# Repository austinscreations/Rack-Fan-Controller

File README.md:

# Rack-Fan-Controller
a controller that can monitor temperature in rack enclosures and control fans

2023-10-25 files have been updated and all JLCPCB PCBa files have now been included.

fan controller is a 4 layer PCB

breakout is 2 layers

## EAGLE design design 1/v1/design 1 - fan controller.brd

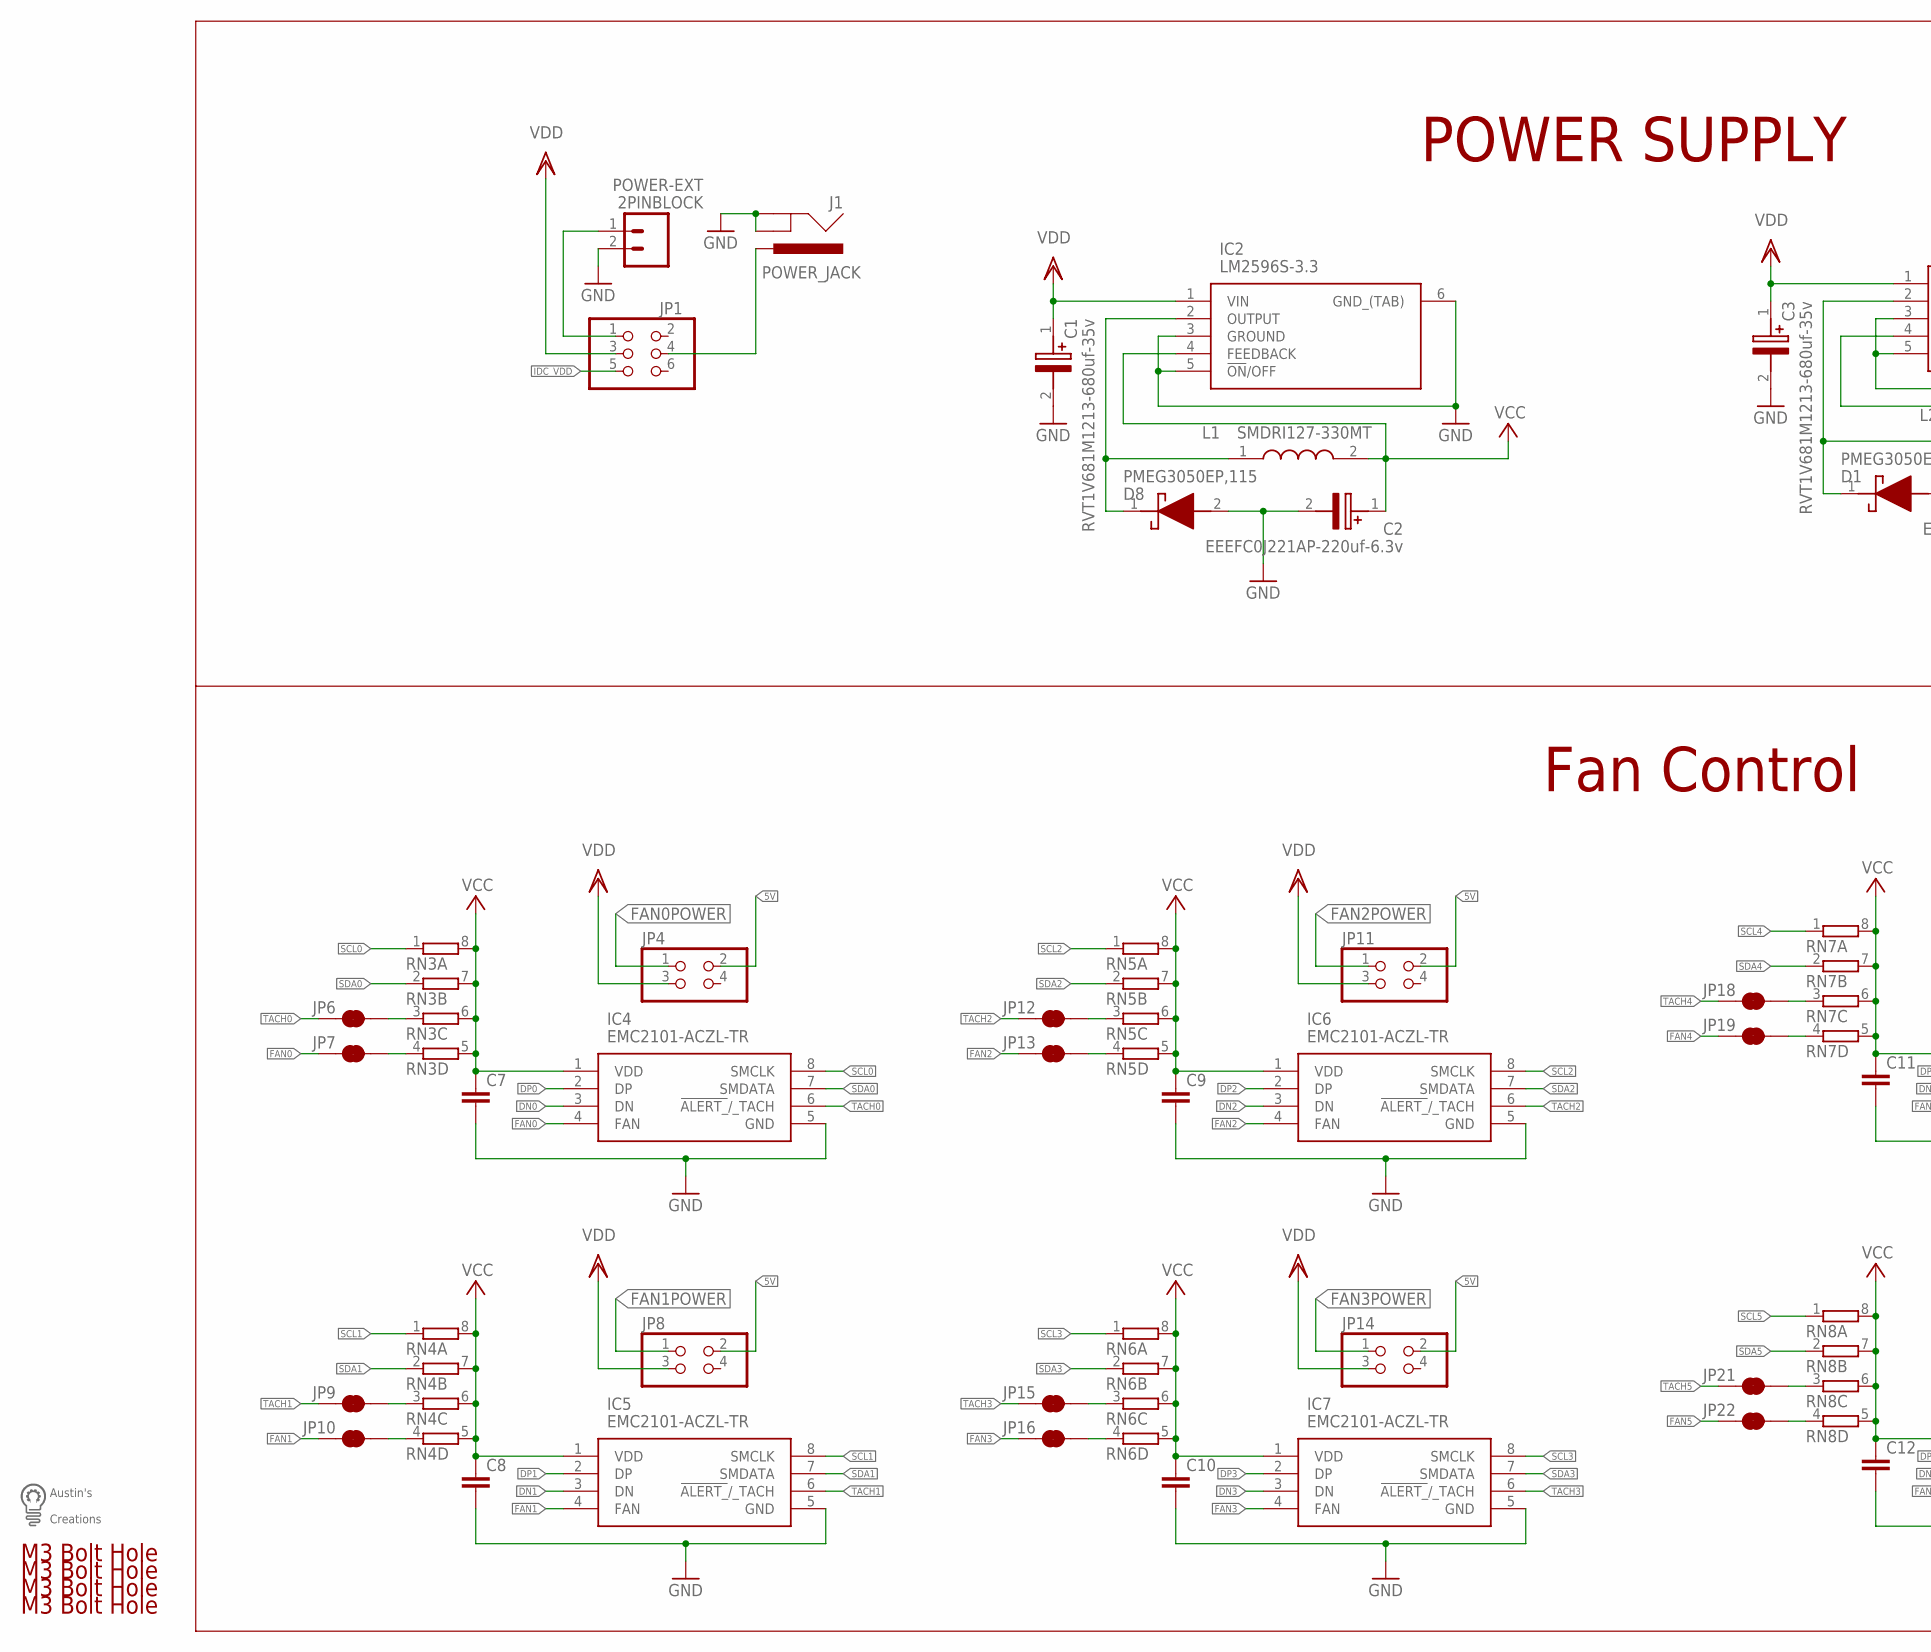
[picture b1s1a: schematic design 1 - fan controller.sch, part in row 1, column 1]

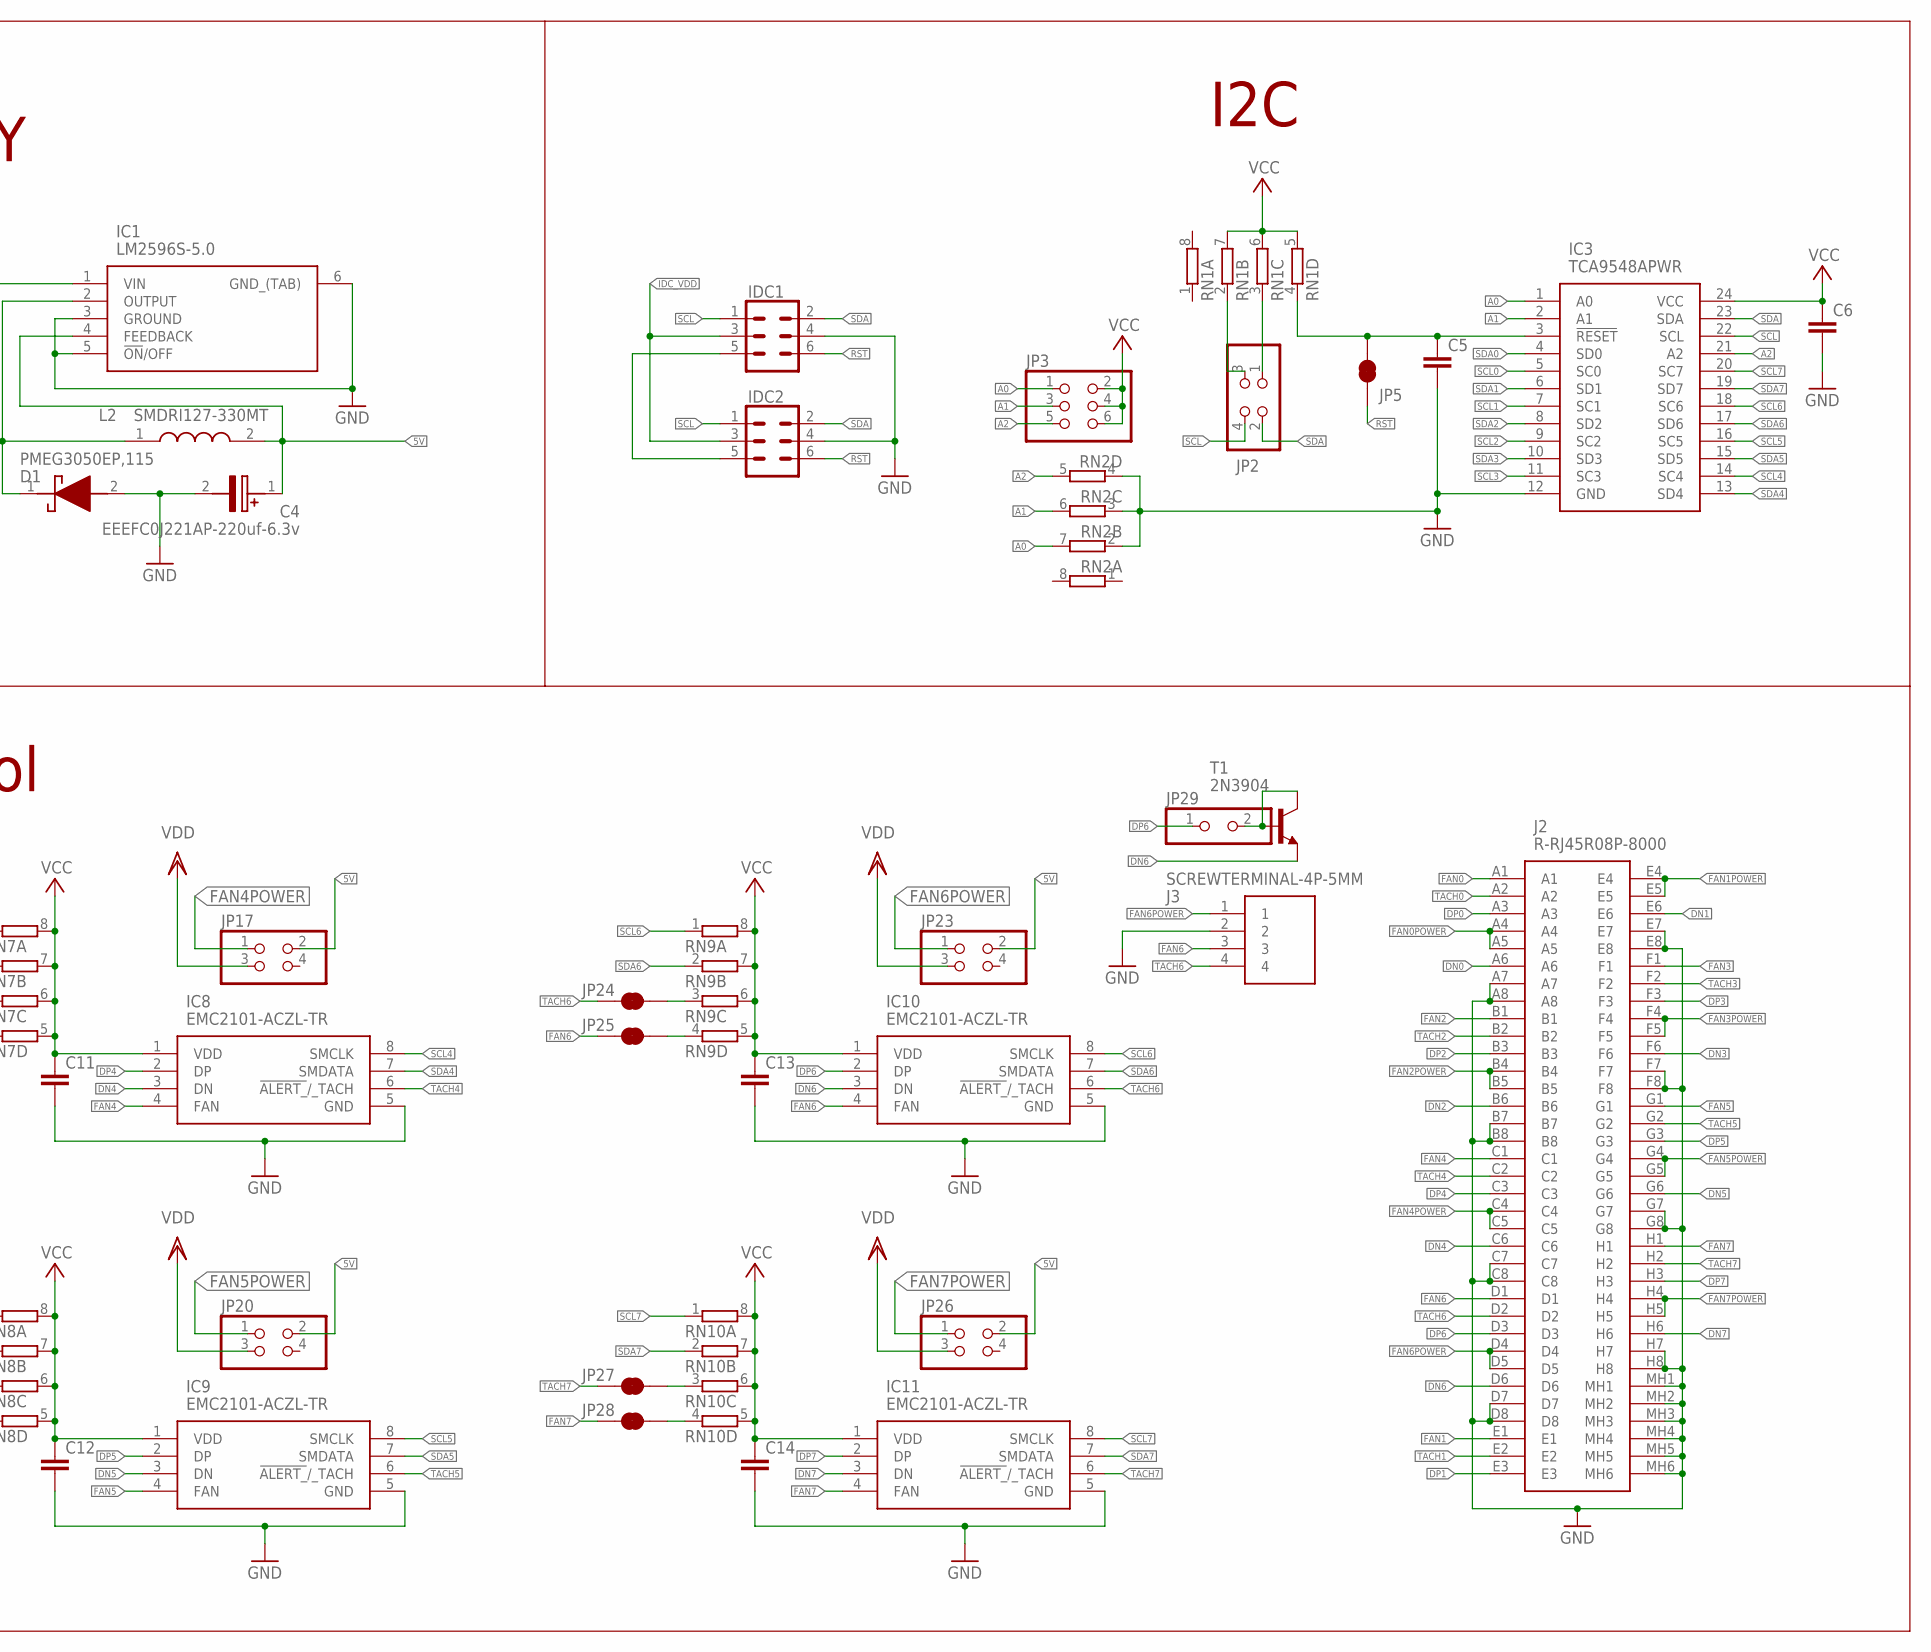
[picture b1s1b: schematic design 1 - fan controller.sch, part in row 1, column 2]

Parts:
C1, C3: RVT1V681M1213-680uf-35v; CAPAE1350X1400N
C2, C4: EEEFC0J221AP-220uf-6.3v; CAPAE830X650N
C5, C6, C7, C8, C9, C10, C11, C12, C13, C14: C-EUC0603; C0603
D1, D8: PMEG3050EP,115; PMEG3050EP115
IC1: LM2596S-5.0; TO170P1435X465-6N
IC2: LM2596S-3.3; TO170P1435X465-6N
IC3: TCA9548APWR; SOP65P640X120-24N
IC4, IC5, IC6, IC7, IC8, IC9, IC10, IC11: EMC2101-ACZL-TR; SOP65P490X110-8N
IDC1, IDC2: CONN_03X2SHROUD; 2X3-SHROUDED
J1: POWER_JACK; POWER_JACK_PTH
J2: R-RJ45R08P-8000; RRJ45R08P8000
J3: SCREWTERMINAL-4P-5MM
JP1, JP3: PINHD-2X3; 2X03
JP2, JP4, JP8, JP11, JP14, JP17, JP20, JP23, JP26: PINHD-2X2; 2X02
JP5, JP6, JP7, JP9, JP10, JP12, JP13, JP15, JP16, JP18, JP19, JP21, JP22, JP24, JP25, JP27, JP28: JUMPER-SMT_2_NC_TRACE_SILK; SMT-JUMPER_2_NC_TRACE_SILK
JP29: PINHD-1X2; 1X02
L1, L2: SMDRI127-330MT; INDPM120120X800N
POWER-EXT: 2PINBLOCK; SCREWTERMINAL-5MM-2
RN1, RN2, RN3, RN4, RN5, RN6, RN7, RN8, RN9, RN10: 4R-N0603-ARC; 0603-ARC
T1: 2N3904; TO92
U$1, U$2, U$3, U$4: M3BOLTHOLE
U$5: LOGOMED

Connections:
5V: C4.1 (+), IC1.4 (FEEDBACK), JP4.2, JP8.2, JP11.2, JP14.2, JP17.2, JP20.2, JP23.2, JP26.2, L2.2
$2: JP29.2, T1.1 (C), T1.2 (B)
A0: IC3.1 (A0), JP3.1, RN2.7 (2)
A1: IC3.2 (A1), JP3.3, RN2.6 (2)
A2: IC3.21 (A2), JP3.5, RN2.5 (2)
DN0: IC4.3 (DN), J2.A6
DN1: IC5.3 (DN), J2.E6
DN2: IC6.3 (DN), J2.B6
DN3: IC7.3 (DN), J2.F6
DN4: IC8.3 (DN), J2.C6
DN5: IC9.3 (DN), J2.G6
DN6: IC10.3 (DN), J2.D6, T1.3 (E)
DN7: IC11.3 (DN), J2.H6
DP0: IC4.2 (DP), J2.A3
DP1: IC5.2 (DP), J2.E3
DP2: IC6.2 (DP), J2.B3
DP3: IC7.2 (DP), J2.F3
DP4: IC8.2 (DP), J2.C3
DP5: IC9.2 (DP), J2.G3
DP6: IC10.2 (DP), J2.D3, JP29.1
DP7: IC11.2 (DP), J2.H3
FAN0: IC4.4 (FAN), J2.A1, JP7.1
FAN0POWER: J2.A4, J2.A5, JP4.1
FAN1: IC5.4 (FAN), J2.E1, JP10.1
FAN1POWER: J2.E4, J2.E5, JP8.1
FAN2: IC6.4 (FAN), J2.B1, JP13.1
FAN2POWER: J2.B4, J2.B5, JP11.1
FAN3: IC7.4 (FAN), J2.F1, JP16.1
FAN3POWER: J2.F4, J2.F5, JP14.1
FAN4: IC8.4 (FAN), J2.C1, JP19.1
FAN4POWER: J2.C4, J2.C5, JP17.1
FAN5: IC9.4 (FAN), J2.G1, JP22.1
FAN5POWER: J2.G4, J2.G5, JP20.1
FAN6: IC10.4 (FAN), J2.D1, J3.3, JP25.1
FAN6POWER: J2.D4, J2.D5, J3.1, JP23.1
FAN7: IC11.4 (FAN), J2.H1, JP28.1
FAN7POWER: J2.H4, J2.H5, JP26.1
GND: C1.2 (-), C2.2 (-), C3.2 (-), C4.2 (-), C5.2, C6.2, C7.2, C8.2, C9.2, C10.2, C11.2, C12.2, C13.2, C14.2, D1.2 (A), D8.2 (A), IC1.3 (GROUND), IC1.5 (!ON!/OFF), IC1.6 (GND_(TAB)), IC2.3 (GROUND), IC2.5 (!ON!/OFF), IC2.6 (GND_(TAB)), IC3.12 (GND), IC4.5 (GND), IC5.5 (GND), IC6.5 (GND), IC7.5 (GND), IC8.5 (GND), IC9.5 (GND), IC10.5 (GND), IC11.5 (GND), IDC1.4, IDC2.4, J1.GND, J1.GNDBREAK, J2.A7, J2.A8, J2.B7, J2.B8, J2.C7, J2.C8, J2.D7, J2.D8, J2.E7, J2.E8, J2.F7, J2.F8, J2.G7, J2.G8, J2.H7, J2.H8, J2.MH1, J2.MH2, J2.MH3, J2.MH4, J2.MH5, J2.MH6, J3.2, POWER-EXT.2, RN2.2 (1), RN2.3 (1), RN2.4 (1)
IDC_VDD: IDC1.3, IDC2.3, JP1.5
unnamed: D1.1 (K), IC1.2 (OUTPUT), L2.1
unnamed: C5.1, IC3.3 (!RESET), JP5.2, RN1.4 (1)
unnamed: JP6.2, RN3.3 (1)
unnamed: JP1.1, POWER-EXT.1
unnamed: JP7.2, RN3.4 (1)
unnamed: J1.PWR, JP1.4
unnamed: JP9.2, RN4.3 (1)
unnamed: JP10.2, RN4.4 (1)
unnamed: JP12.2, RN5.3 (1)
unnamed: JP13.2, RN5.4 (1)
unnamed: JP15.2, RN6.3 (1)
unnamed: IDC1.5, IDC2.5
unnamed: JP16.2, RN6.4 (1)
unnamed: JP18.2, RN7.3 (1)
unnamed: JP19.2, RN7.4 (1)
unnamed: JP21.2, RN8.3 (1)
unnamed: JP22.2, RN8.4 (1)
unnamed: JP24.2, RN9.3 (1)
unnamed: JP25.2, RN9.4 (1)
unnamed: D8.1 (K), IC2.2 (OUTPUT), L1.1
unnamed: JP27.2, RN10.3 (1)
unnamed: JP28.2, RN10.4 (1)
unnamed: JP2.3, RN1.2 (1)
unnamed: JP2.1, RN1.3 (1)
RST: IDC1.6, IDC2.6, JP5.1
SCL: IC3.22 (SCL), IDC1.1, IDC2.1, JP2.4
SCL0: IC3.5 (SC0), IC4.8 (SMCLK), RN3.1
SCL1: IC3.7 (SC1), IC5.8 (SMCLK), RN4.1
SCL2: IC3.9 (SC2), IC6.8 (SMCLK), RN5.1
SCL3: IC3.11 (SC3), IC7.8 (SMCLK), RN6.1
SCL4: IC3.14 (SC4), IC8.8 (SMCLK), RN7.1
SCL5: IC3.16 (SC5), IC9.8 (SMCLK), RN8.1
SCL6: IC3.18 (SC6), IC10.8 (SMCLK), RN9.1
SCL7: IC3.20 (SC7), IC11.8 (SMCLK), RN10.1
SDA: IC3.23 (SDA), IDC1.2, IDC2.2, JP2.2
SDA0: IC3.4 (SD0), IC4.7 (SMDATA), RN3.2 (1)
SDA1: IC3.6 (SD1), IC5.7 (SMDATA), RN4.2 (1)
SDA2: IC3.8 (SD2), IC6.7 (SMDATA), RN5.2 (1)
SDA3: IC3.10 (SD3), IC7.7 (SMDATA), RN6.2 (1)
SDA4: IC3.13 (SD4), IC8.7 (SMDATA), RN7.2 (1)
SDA5: IC3.15 (SD5), IC9.7 (SMDATA), RN8.2 (1)
SDA6: IC3.17 (SD6), IC10.7 (SMDATA), RN9.2 (1)
SDA7: IC3.19 (SD7), IC11.7 (SMDATA), RN10.2 (1)
TACH0: IC4.6 (!ALERT_!/_TACH), J2.A2, JP6.1
TACH1: IC5.6 (!ALERT_!/_TACH), J2.E2, JP9.1
TACH2: IC6.6 (!ALERT_!/_TACH), J2.B2, JP12.1
TACH3: IC7.6 (!ALERT_!/_TACH), J2.F2, JP15.1
TACH4: IC8.6 (!ALERT_!/_TACH), J2.C2, JP18.1
TACH5: IC9.6 (!ALERT_!/_TACH), J2.G2, JP21.1
TACH6: IC10.6 (!ALERT_!/_TACH), J2.D2, J3.4, JP24.1
TACH7: IC11.6 (!ALERT_!/_TACH), J2.H2, JP27.1
VCC: C2.1 (+), C6.1, C7.1, C8.1, C9.1, C10.1, C11.1, C12.1, C13.1, C14.1, IC2.4 (FEEDBACK), IC3.24 (VCC), IC4.1 (VDD), IC5.1 (VDD), IC6.1 (VDD), IC7.1 (VDD), IC8.1 (VDD), IC9.1 (VDD), IC10.1 (VDD), IC11.1 (VDD), JP3.2, JP3.4, JP3.6, L1.2, RN1.5 (2), RN1.6 (2), RN1.7 (2), RN3.5 (2), RN3.6 (2), RN3.7 (2), RN3.8 (2), RN4.5 (2), RN4.6 (2), RN4.7 (2), RN4.8 (2), RN5.5 (2), RN5.6 (2), RN5.7 (2), RN5.8 (2), RN6.5 (2), RN6.6 (2), RN6.7 (2), RN6.8 (2), RN7.5 (2), RN7.6 (2), RN7.7 (2), RN7.8 (2), RN8.5 (2), RN8.6 (2), RN8.7 (2), RN8.8 (2), RN9.5 (2), RN9.6 (2), RN9.7 (2), RN9.8 (2), RN10.5 (2), RN10.6 (2), RN10.7 (2), RN10.8 (2)
VDD: C1.1 (+), C3.1 (+), IC1.1 (VIN), IC2.1 (VIN), JP1.3, JP4.3, JP8.3, JP11.3, JP14.3, JP17.3, JP20.3, JP23.3, JP26.3

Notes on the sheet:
I2C
POWER SUPPLY
Fan Control

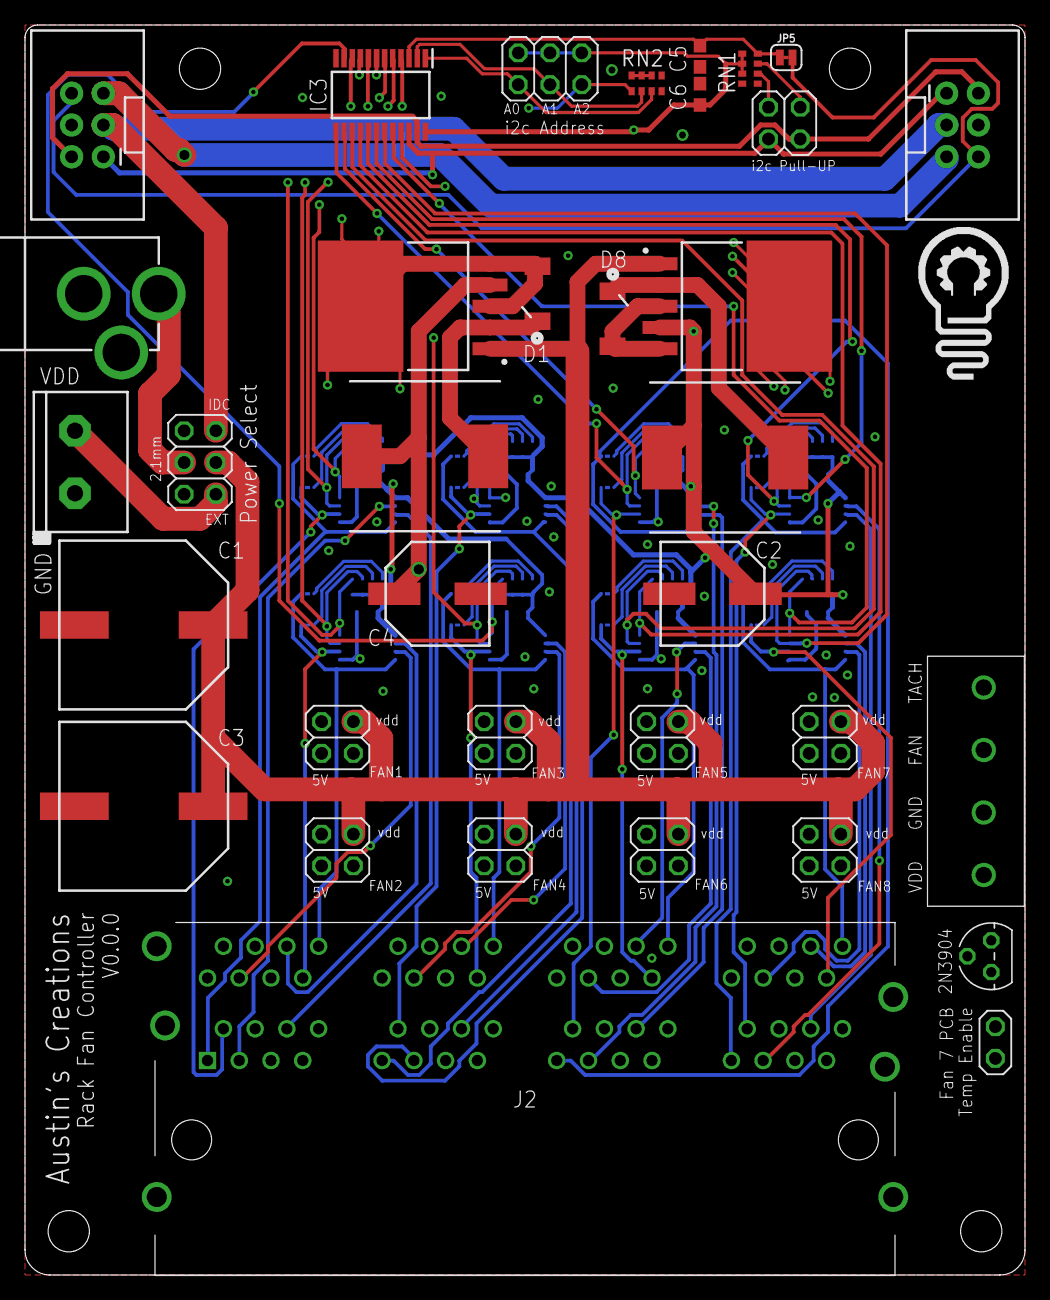
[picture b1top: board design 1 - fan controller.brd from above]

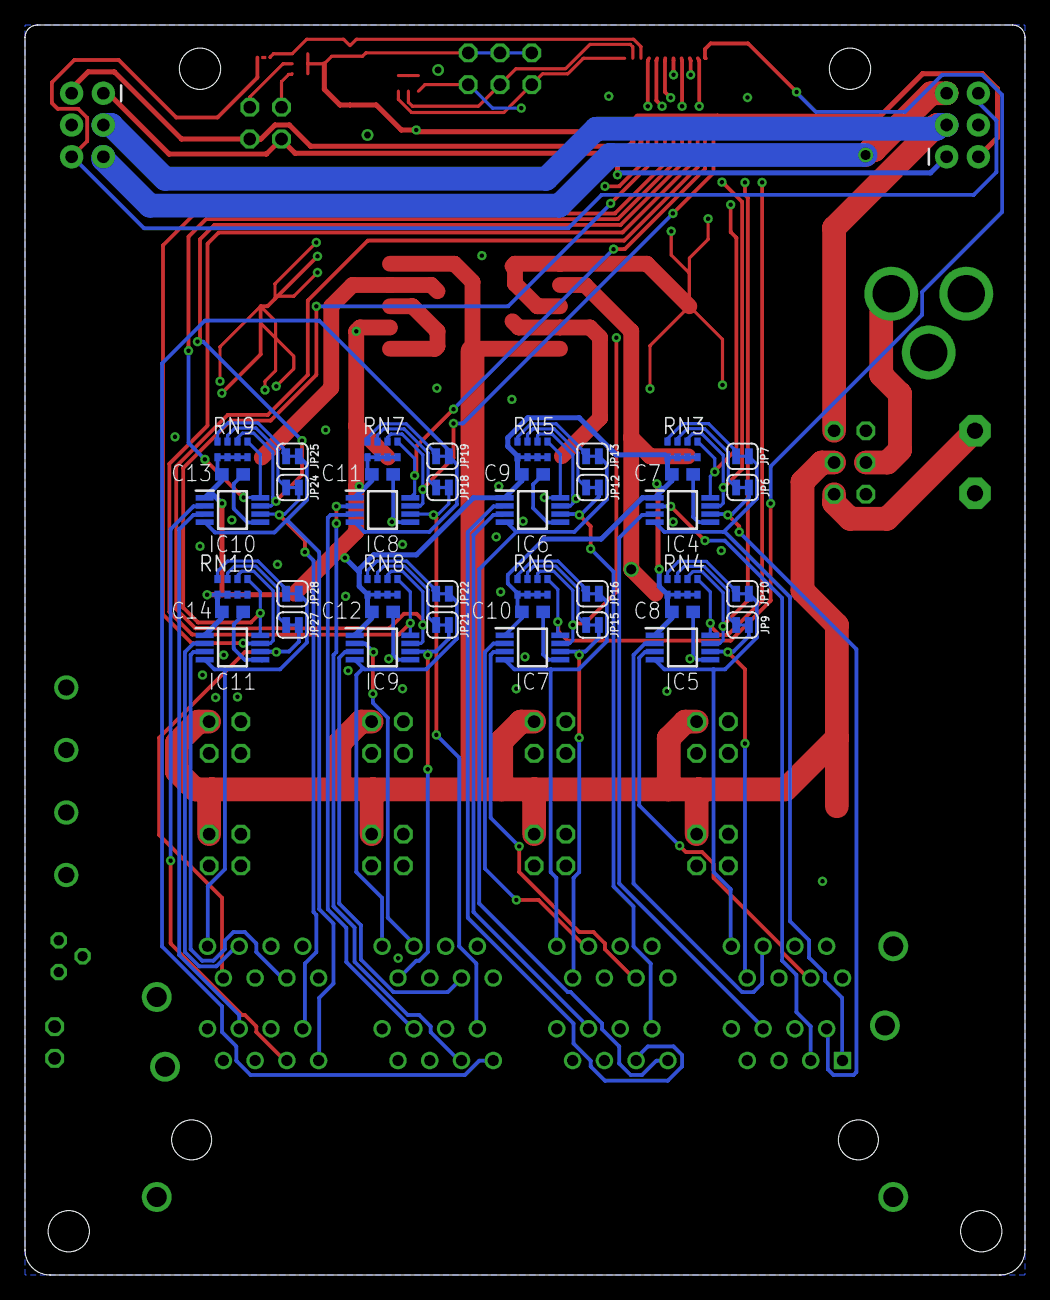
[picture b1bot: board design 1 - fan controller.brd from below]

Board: 4 copper layers, 80.0 x 100.0 mm, 80 parts (40 on the bottom side), 92 nets.

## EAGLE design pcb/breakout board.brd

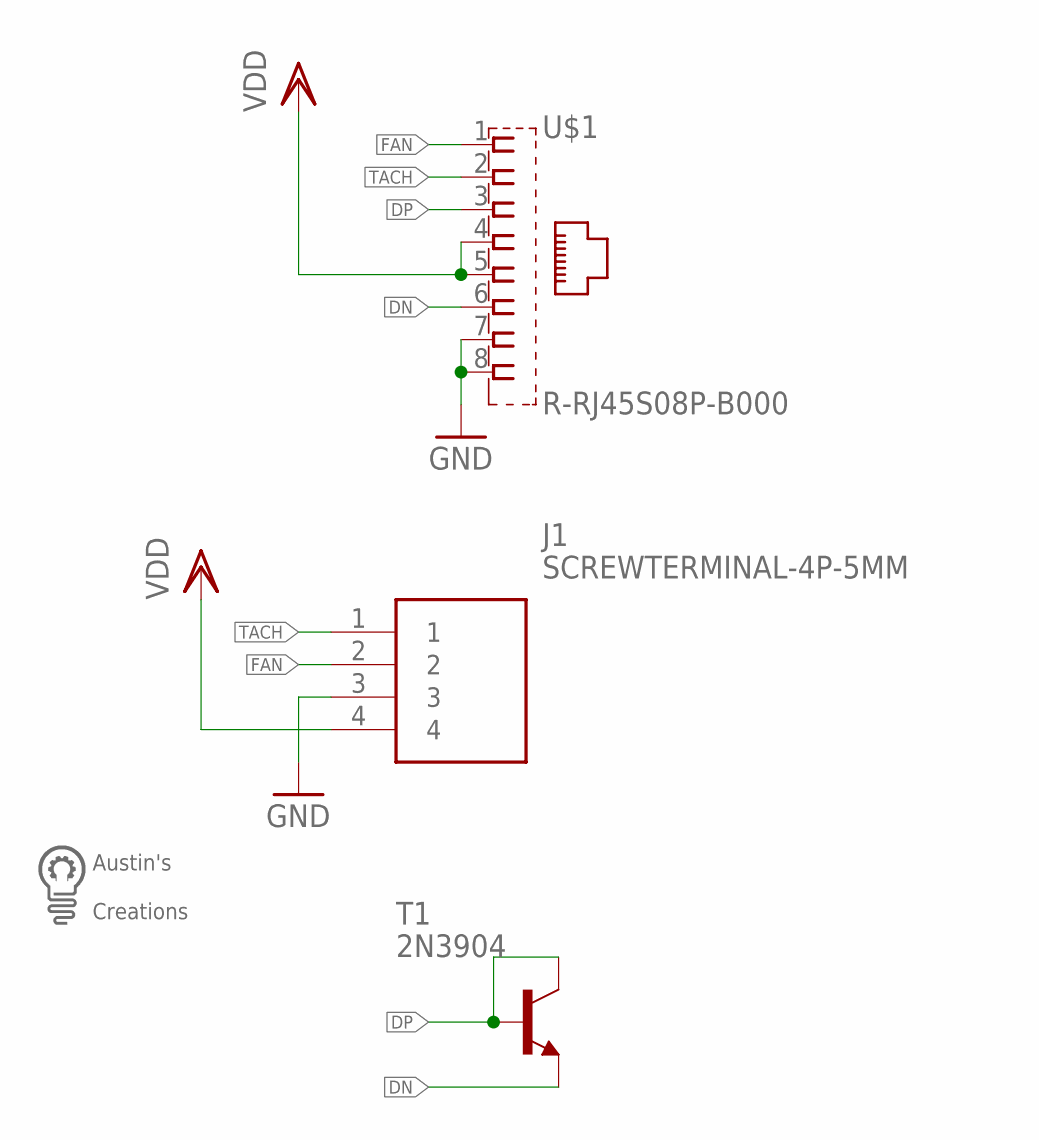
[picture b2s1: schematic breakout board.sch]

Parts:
J1: SCREWTERMINAL-4P-5MM
T1: 2N3904; TO92
U$1: R-RJ45S08P-B000
U$2: LOGOMED

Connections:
DN: T1.3 (E), U$1.6
DP: T1.1 (C), T1.2 (B), U$1.3
FAN: J1.2, U$1.1
GND: J1.3, U$1.7, U$1.8
TACH: J1.1, U$1.2
VDD: J1.4, U$1.4, U$1.5

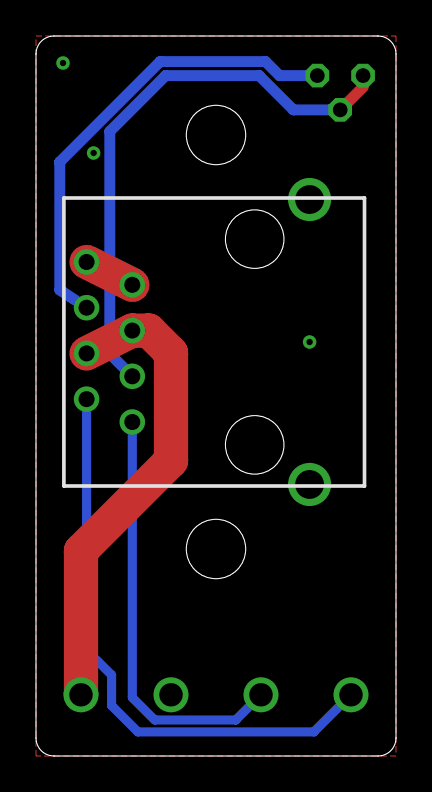
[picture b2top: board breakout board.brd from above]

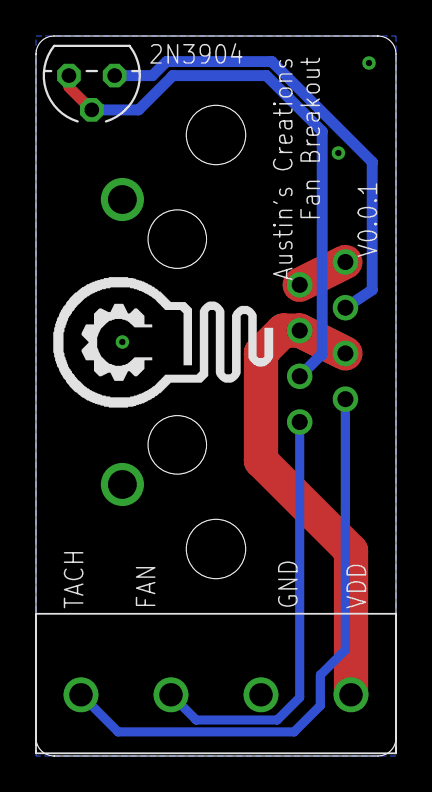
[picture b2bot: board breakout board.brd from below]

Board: 2 copper layers, 20.0 x 40.0 mm, 4 parts (3 on the bottom side), 6 nets.

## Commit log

2023-05-07 add warning

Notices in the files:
parts and their libraries:
SparkFun-Jumpers: Licensing: Creative Commons ShareAlike 4.0 International - https://creativecommons.org/licenses/by-sa/4.0
